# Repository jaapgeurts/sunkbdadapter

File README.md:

## Sun Type 6 Keyboard Adapter

This software is a Sun Type 6 UART Keyboard to USB adapter. It lets you connect a sun type 6 non-usb keyboard to your PC in a USB port
using an Arduino Micro. The Arduino will present itself as a real Sun Type 6 USB keyboard.

## Connecting the keyboard

Connect your Sun keyboard as follows:

See this page for a description of the DIN connector

https://github.com/benr/SunType5_ArduinoAdapter

Then connect From KDB to pin 9 on the Arduino, and To KBD to pin 8 on the Arduino.
Hook up power and ground.

## Building

You need to download and install [https://github.com/abcminiuser/lufa](LUFA]).

Adjust the makefile and point it to the LUFA_PATH variable to the correct directory.

Then issue the following command:

`$ make`

Make sure an Arduino Micro/Leonardo (or any other AVR 32u4 board is attached)

`$ make flash`

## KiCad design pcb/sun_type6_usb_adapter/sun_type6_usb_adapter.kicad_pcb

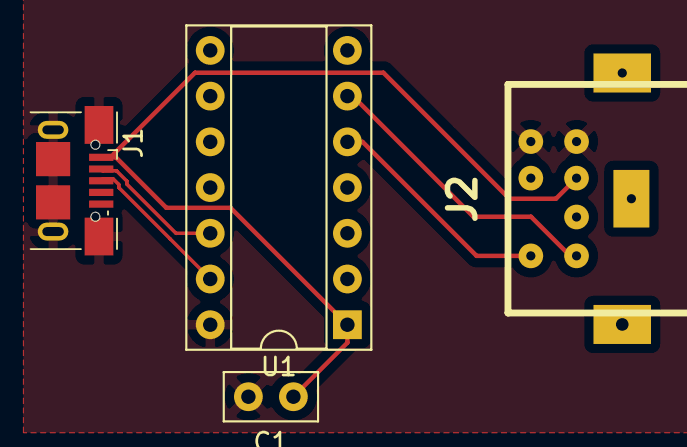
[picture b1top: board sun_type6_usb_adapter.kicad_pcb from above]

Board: 2 copper layers, 4 parts (0 on the bottom side), 6 nets.

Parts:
C1: 100n; C_Disc_D5.0mm_W2.5mm_P2.50mm
J1: USB_B_Micro; USB_Micro_B_XKB_U254-05XX-4BH83-X-X-S
J2: Mini-DIN-8; Mini_din7
U1: PIC16F1454-IP; DIP-14_W7.62mm_Socket

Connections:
+5V: C1.1, J1.1, J2.3, U1.1
/D+: J1.3, U1.13
/D-: J1.2, U1.12
/RXD: J2.6, U1.5
/TXD: J2.5, U1.6
GND: C1.2, J1.5, J1.6, J2.1, J2.2, U1.14

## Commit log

2020-04-22 Create LICENSE
2020-04-22 Added last files
2020-04-24 Improved modifier detection code
2020-04-24 Prototype working
2020-04-27 Improved from libusb to udev
2020-04-27 Works. Can control LEDs
2020-04-27 Reorganized folder structure
2020-04-27 Reorganized folders
2020-04-27 Moved license and readme
2020-05-03 Keypad plus sends minus key. Fixed
2020-05-11 Fixed power consumption report and power source report
2020-10-14 Initial commit of firmware for pic16f1454 adapter, add adapter pcb
2020-10-18 Working without NKRO
2020-10-18 Working with all keys and NKRO
